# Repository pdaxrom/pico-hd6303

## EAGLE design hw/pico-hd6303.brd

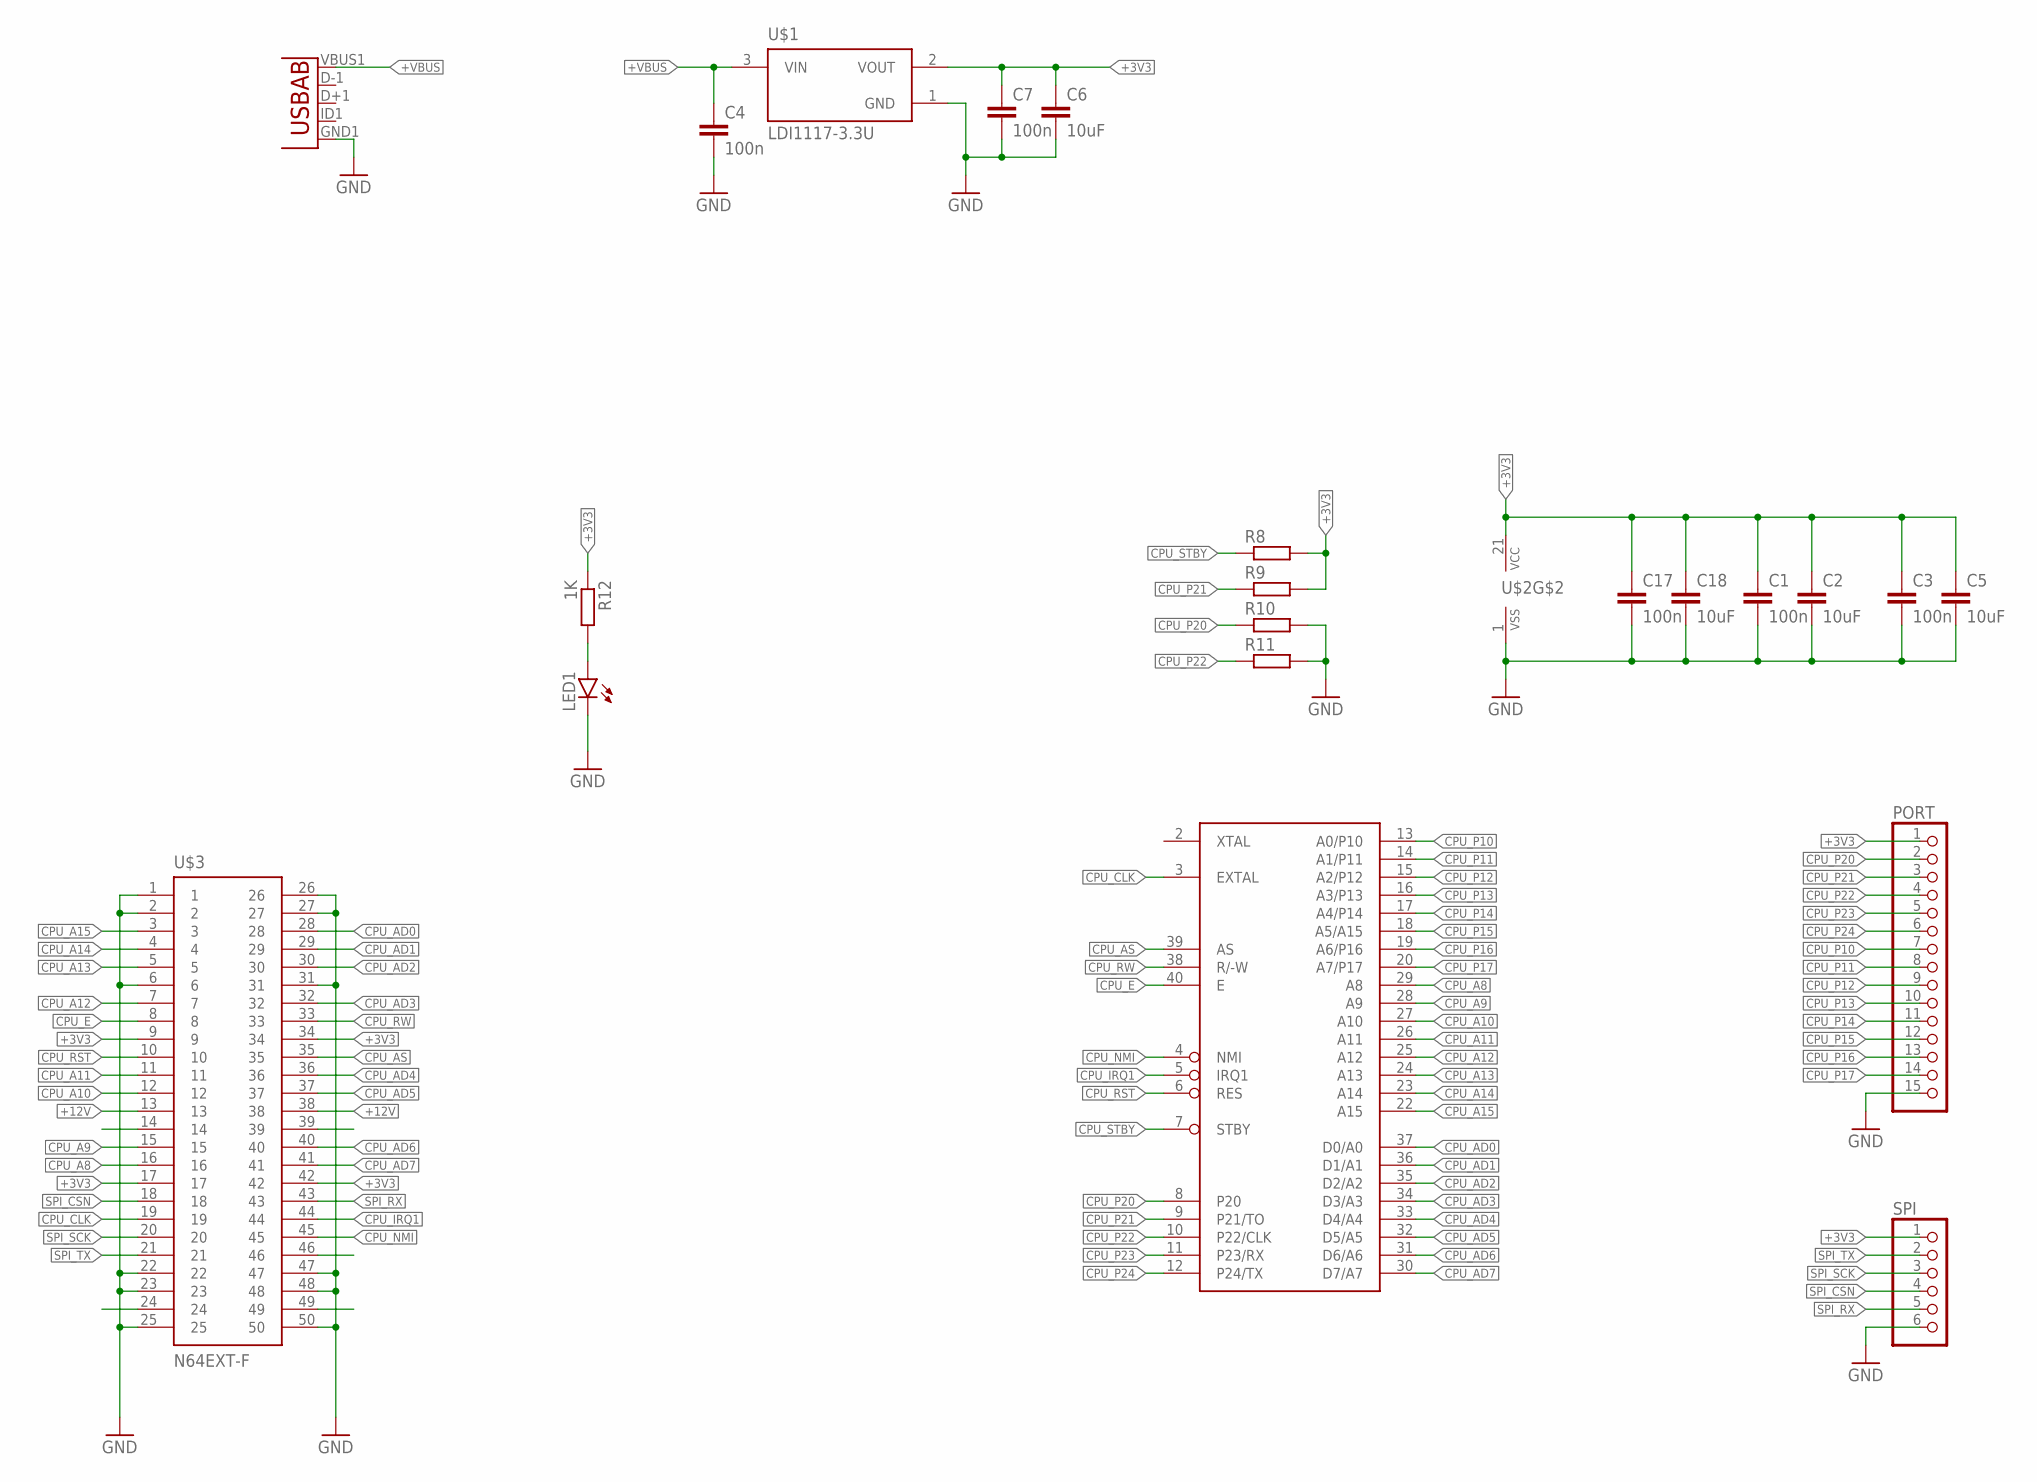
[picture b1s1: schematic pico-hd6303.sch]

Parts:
C1, C3, C17: 100n; C0603
C2, C5, C6, C18: 10uF; C0805
C4, C7: 100n; C0402
LED1: LED5MM
PORT: PINHD-1X15; 1X15
R8, R9, R10, R11: R-EU_R0603; R0603
R12: 1K; R0603
SPI: PINHD-1X6; 1X06
U2: USB""; USB-MICRO-SMD
U$1: LDI1117-3.3U
U$2: HD63B03PRP; DIL40
U$3: N64EXT-F; N64F

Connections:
+3V3: C1.1, C2.1, C3.1, C5.1, C6.1, C7.1, C17.1, C18.1, PORT.1, R8.2, R9.2, R12.1, SPI.1, U$1.2 (VOUT), U$2.21 (VCC), U$3.9, U$3.17, U$3.34, U$3.42
+12V: U$3.13, U$3.38
+VBUS: C4.1, U2.VBUS1 (VBUS), U$1.3 (VIN)
CPU_A8: U$2.29 (A8), U$3.16
CPU_A9: U$2.28 (A9), U$3.15
CPU_A10: U$2.27 (A10), U$3.12
CPU_A11: U$2.26 (A11), U$3.11
CPU_A12: U$2.25 (A12), U$3.7
CPU_A13: U$2.24 (A13), U$3.5
CPU_A14: U$2.23 (A14), U$3.4
CPU_A15: U$2.22 (A15), U$3.3
CPU_AD0: U$2.37 (D0/A0), U$3.28
CPU_AD1: U$2.36 (D1/A1), U$3.29
CPU_AD2: U$2.35 (D2/A2), U$3.30
CPU_AD3: U$2.34 (D3/A3), U$3.32
CPU_AD4: U$2.33 (D4/A4), U$3.36
CPU_AD5: U$2.32 (D5/A5), U$3.37
CPU_AD6: U$2.31 (D6/A6), U$3.40
CPU_AD7: U$2.30 (D7/A7), U$3.41
CPU_AS: U$2.39 (AS), U$3.35
CPU_CLK: U$2.3 (EXTAL), U$3.19
CPU_E: U$2.40 (E), U$3.8
CPU_IRQ1: U$2.5 (IRQ1), U$3.44
CPU_NMI: U$2.4 (NMI), U$3.45
CPU_P10: PORT.7, U$2.13 (A0/P10)
CPU_P11: PORT.8, U$2.14 (A1/P11)
CPU_P12: PORT.9, U$2.15 (A2/P12)
CPU_P13: PORT.10, U$2.16 (A3/P13)
CPU_P14: PORT.11, U$2.17 (A4/P14)
CPU_P15: PORT.12, U$2.18 (A5/A15)
CPU_P16: PORT.13, U$2.19 (A6/P16)
CPU_P17: PORT.14, U$2.20 (A7/P17)
CPU_P20: PORT.2, R10.1, U$2.8 (P20)
CPU_P21: PORT.3, R9.1, U$2.9 (P21/TO)
CPU_P22: PORT.4, R11.1, U$2.10 (P22/CLK)
CPU_P23: PORT.5, U$2.11 (P23/RX)
CPU_P24: PORT.6, U$2.12 (P24/TX)
CPU_RST: U$2.6 (RES), U$3.10
CPU_RW: U$2.38 (R/-W), U$3.33
CPU_STBY: R8.1, U$2.7 (STBY)
GND: C1.2, C2.2, C3.2, C4.2, C5.2, C6.2, C7.2, C17.2, C18.2, LED1.K (C), PORT.15, R10.2, R11.2, SPI.6, U2.GND1 (GND), U$1.1 (GND), U$2.1 (VSS), U$3.1, U$3.2, U$3.6, U$3.22, U$3.23, U$3.25, U$3.26, U$3.27, U$3.31, U$3.47, U$3.48, U$3.50
unnamed: LED1.A, R12.2
SPI_CSN: SPI.4, U$3.18
SPI_RX: SPI.5, U$3.43
SPI_SCK: SPI.3, U$3.20
SPI_TX: SPI.2, U$3.21

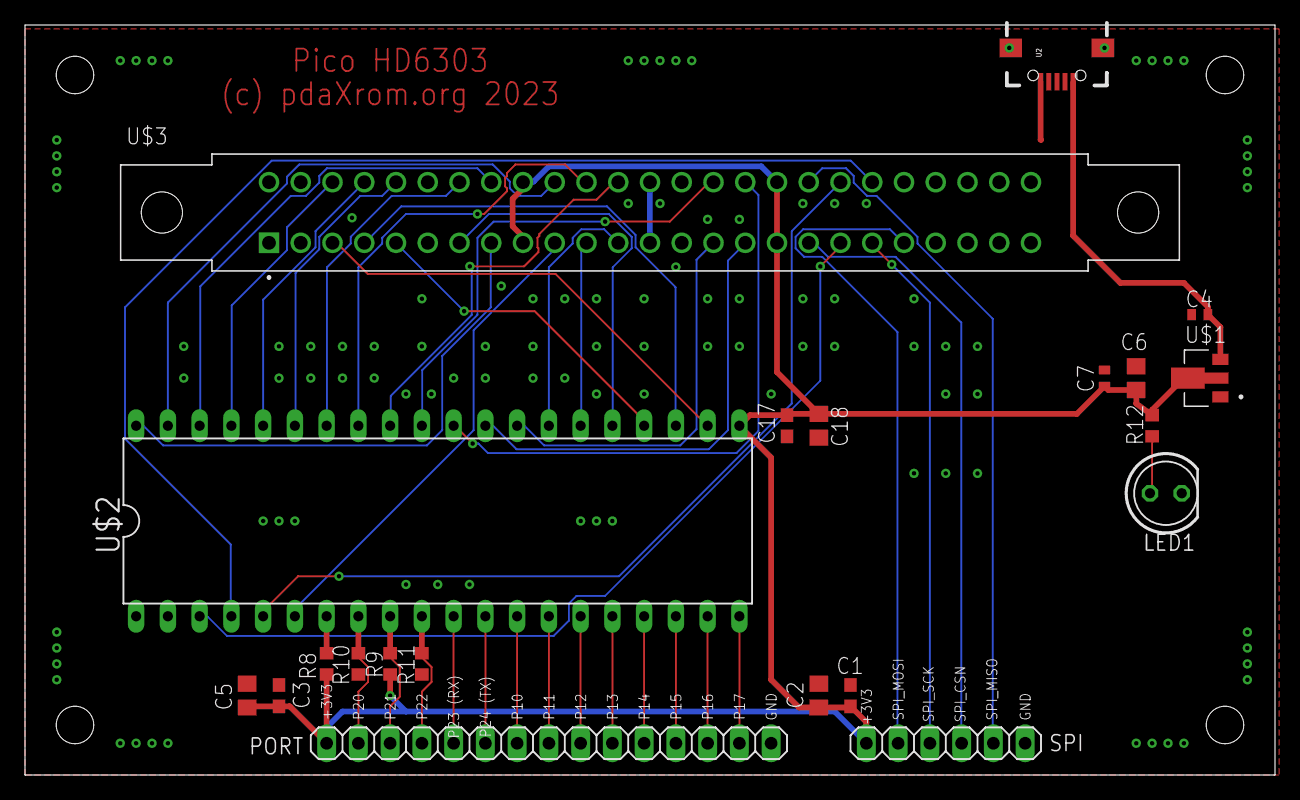
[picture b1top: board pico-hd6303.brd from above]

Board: 2 copper layers, 100.0 x 60.0 mm, 21 parts (0 on the bottom side), 46 nets.

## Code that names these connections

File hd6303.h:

#pragma once

#ifdef PICO_HD6303_HW

#define CPU_AD0  0
#define CPU_AD1  1
#define CPU_AD2  2
#define CPU_AD3  3
#define CPU_AD4  4
#define CPU_AD5  5
#define CPU_AD6  6
#define CPU_AD7  7
#define CPU_A8   8
#define CPU_A9   9
#define CPU_A10 10
#define CPI_A11 11
#define CPU_A12 12
#define CPU_A13 13
#define CPU_A14 14
#define CPU_A15 15
#define CPU_RW  16
#define CPU_AS  17
#define CPU_E   18
#define CPU_RST 19
#define CPU_CLK 24
#define CPU_NMI 26
#define CPU_IRQ 27

#define LED_PIN 25

#define SPI0_MISO 20
#define SPI0_CSN  21
#define SPI0_SCK  22
#define SPI0_MOSI 23

#define UART_TX_PIN (28)
#define UART_RX_PIN (29)
#define UART_ID     uart0
#define BAUD_RATE   9600

#else

/*
 * Minimal configuration:
 * NMI (4), IRQ1 (5), STBY (7), P21 (9) - +3.3v
 * P20 (8), P22 (10), VSS (1) - GND
 * VCC (21) - +3.3V
 */

#define CPU_AD0  0
#define CPU_AD1  1
#define CPU_AD2  2
#define CPU_AD3  3
#define CPU_AD4  4
#define CPU_AD5  5
#define CPU_AD6  6
#define CPU_AD7  7
#define CPU_A8   8
#define CPU_A9   9
#define CPU_A10 10
#define CPI_A11 11
#define CPU_A12 12
#define CPU_A13 13
#define CPU_A14 14
#define CPU_A15 15
#define CPU_RW  18
#define CPU_AS  19
#define CPU_E   20
#define CPU_RST 22
#define CPU_CLK 21

#define LED_PIN 25

#define UART_TX_PIN (16)
#define UART_RX_PIN (17)
#define UART_ID     uart0
#define BAUD_RATE   9600

#endif

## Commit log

2023-05-10 initial
2023-05-11 toolchain
2023-05-11 use usb cdc as uart, added uart bootrom
2023-05-11 git submodule updated
2023-05-12 mapping real hardware uart to cpu bus to get working CPU on 2MHz
2023-05-12 updated pins to use gp16/gp17 as UART0
2023-05-12 missed power pins for minimal configuration
2023-06-01 pico hd6303 hardware board reused n64cart as cpu control logic, i/o and rom/ram
2024-07-31 n64cart support
2024-07-31 support for pico/n64cart hardware
2024-07-31 use 1MHz for CPU and 9600 for uart
